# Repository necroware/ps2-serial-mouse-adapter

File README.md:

# PS/2 to Serial Mouse Adapter

Many retro PCs were used with serial port mouse and don't have any PS/2 ports.
Unfortunately most of the serial mice are broken or expensive today. Furthermore
they were mechanical devices with a heavy steel ball to track the movement. This
mechanics got dirty quite fast and was not the best user experience anyway. A
better solution are optical PS/2 mice, most of which unfortunately would not 
work on a serial port. This adapter can be used to connect such a PS/2 mouse to
a serial port of a retro PC.The Adapter is made from through-hole parts only, so
it is very easy to solder and due to Arduino based solution, it is also a very
nice device for tinkering, experimenting and learning about mouse protocols.

## How does it work?

The serial port on the computer communicates with the mouse using basically two
pins - RTS and RX. RTS is used for notification and RX for the actual data
transfer, which contains mouse position, buttons state etcetera. A standard PS/2
mouse on the other hand uses completely incompatible protocol and transfers the
data between the mouse and the computer using the Data and Clock pins. If we
want to connect a PS/2 mouse, to a serial port, we need some instance in
between, to translate between the two different protocols. In this adapter the
translation is done using an Arduino Mini. However, there is another problem.
PS/2 mouse  protocol uses so called TTL logic, which simply means, that the
voltage of 0V means a logical zero and 5V means a logical one. TTL logic is what
Arduino uses as well, but a serial port, or also called RS232, uses another
voltage levels. Any voltage below -3V is a logical one and a voltage above +3V
is a logical zero. So, it is not possible to connect Arduino output directly to
the serial port. It simply will not work and needs another translator, which
converts TTL voltage level to RS232 levels. In this adapter such conversion is
made by a well known MAX232 IC. The software is written in C/C++, it is a simple
Arduino project, which can be used in Arduino Studio as usual.

## How to use?

This project contains everything you need to build your own adapter. You can
use the gerber files to order a PCB. The list of materials is below. After
soldering the adapter, connect the Arduino Mini using an USB to TTL adapter to
your PC and flash the firmware using the Arduino IDE. If you don't know how to
do that, please refer to the documentation of Arduino. 

**ATTENTION!** *The USB port (PWR1) on the adapter is only for powering the
circuits, it is not a data port!*

Connecting the adapter to the PC is very simple. Plug your PS/2 Mouse into the
adapter, connect a mini USB cable to power the adapter. Plug the adapter into a
serial port of your PC. Turn on the PC and use a serial mouse driver of your
choice. The adapter was tested with Microsoft, Logitech and Cute mouse drivers.
Cute Mouse Driver is part of FreeDos project and is free and open source.

## Jumper Settings

There are two jumpers, which can be used to set different modes. Currently you
can choose between 2- and 3-button mouse modes and select so called remote and
streaming mode. Remote mode sends mouse data all the time and has a better
response times in current implementation. Streaming mode sends only data, when
mouse position or button state changes. Unfortunately, this mode is currently
not in a good shape. It has a higher delay and can result in some timing
issues. However, it is interesting to have it for experimental purpose. Default
values are when the jumpers are unset.

JP1 | Setting |Description
----|---------|------------------------------
1-2 | unset   | 3-button Logitech mouse
1-2 | set     | 2-button Microsoft mouse
3-4 | unset   | remote mode
3-4 | set     | streaming mode (experimental)

## Bill of materials

Reference  |#  |LCSC   |Description
-----------|---|-------|------------------------------------------
U1         |1  |       | Arduino Pro Mini 5V (ATMega168 or better)
U2         |1  |C911187| MAX232 or compatible DIP16 package
RS232      |1  |C141882| DB9 female RS232 port
MOUSE1     |1  |C77848 | PS/2 female port
PWR1       |1  |C46398 | Mini-USB port for power supply
C1-5       |5  |C106448| 1µF electrolytic capacitor
R1         |1  |C57436 | 10kOhm resistor (pull-up)
JP1        |1  |       | 2x2 jumper header (optional)

## Known issues

The code is still in development. It works, but it still has some flaws. Timing
is really important in this project and sometimes mouse drivers seem not to get
a response in time from the adapter. Usually just executing the driver once
again will initialize the mouse.

## Tested Mice

If you test the adapter with a mouse, which is not in this list please consider
to submit a report to improve the compatibility of the adapter.

* Logitech Optical Mouse M-BT58 (USB, PS/2, Optical)
* NagerIT Fair Mouse (USB, PS/2, Optical)
* Typthoon Optical Mouse (USB, PS/2, Optical)
* Microsoft IntelliMouse Optical (USB, PS/2, Optical)
* Microsoft IntelliMouse "Classic" (PS/2, Balled)
* Microsoft Basic Optical Mouse (USB, PS/2, Optical, produced 2021)
* Microsoft Comfort Optical Mouse 300 (USB, PS/2, Optical)
* IBM 33G5430 (PS/2, Mechanical)

## Links

* [PS/2 Mouse Protocol description](https://isdaman.com/alsos/hardware/mouse/ps2interface.htm)
* [More PS/2 Mouse Protocol description](http://www-ug.eecg.utoronto.ca/desl/nios_devices_SoC/datasheets/PS2%20Protocol.htm)
* [Serial Mouse Protocol description](https://linux.die.net/man/4/mouse)
* [Cute Mouse Driver](http://cutemouse.sourceforge.net)

## Special Thanks
* creopard from dosreloaded.de for testing with MS IntelliMouse Optical
* moravec from dosreloaded.de for donating the original IBM 33G5430 mechanical mouse

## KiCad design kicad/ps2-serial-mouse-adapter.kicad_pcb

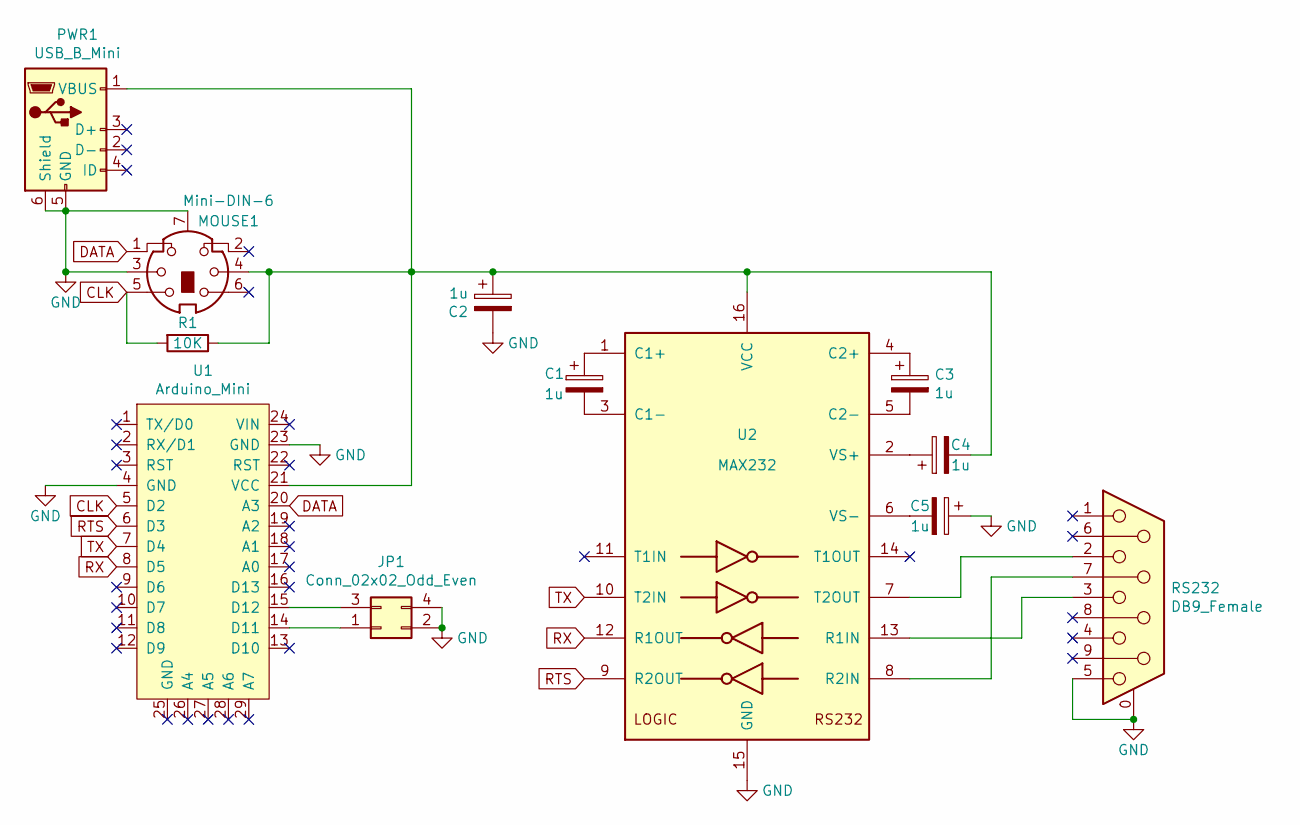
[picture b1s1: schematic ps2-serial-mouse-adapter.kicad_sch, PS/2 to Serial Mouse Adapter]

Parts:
C1, C2, C3, C4, C5: 1u; CP_Radial_D4.0mm_P1.50mm
JP1: Conn_02x02_Odd_Even; PinSocket_2x02_P2.54mm_Vertical
MOUSE1: Mini-DIN-6; Mini_DIN_6_LCSC_C77848; LCSC Part C77848
PWR1: USB_B_Mini; USB_Mini-B-Jing_Extension_LSCS_C46398
R1: 10K; R_Axial_DIN0207_L6.3mm_D2.5mm_P7.62mm_Horizontal; LCSC C57436
RS232: DB9_Female; DSUB-9_Female_Horizontal_P2.77x2.84mm_EdgePinOffset7.70mm_H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
U1: Arduino_Mini; DIP-24_W15.24mm_Socket
U2: MAX232; DIP-16_W7.62mm_Socket; LCSC Part C911187

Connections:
CLK: MOUSE1.5, R1.2, U1.5 (D2)
DATA: MOUSE1.1, U1.20 (A3)
GND: C2.2, C5.1, JP1.2, JP1.4, MOUSE1.3, MOUSE1.7, PWR1.5 (GND), PWR1.6 (Shield), RS232.0 (PAD), RS232.5, U1.4 (GND), U1.23 (GND), U2.15 (GND)
unnamed: C1.1, U2.1 (C1+)
unnamed: C1.2, U2.3 (C1-)
unnamed: C2.1, C4.2, MOUSE1.4, PWR1.1 (VBUS), R1.1, U1.21 (VCC), U2.16 (VCC)
unnamed: C3.1, U2.4 (C2+)
unnamed: C3.2, U2.5 (C2-)
unnamed: C4.1, U2.2 (VS+)
unnamed: C5.2, U2.6 (VS-)
unnamed: JP1.1, U1.14 (D11)
unnamed: JP1.3, U1.15 (D12)
unnamed: RS232.2, U2.7 (T2OUT)
unnamed: RS232.3, U2.13 (R1IN)
unnamed: RS232.7, U2.8 (R2IN)
RTS: U1.6 (D3), U2.9 (R2OUT)
RX: U1.8 (D5), U2.12 (R1OUT)
TX: U1.7 (D4), U2.10 (T2IN)

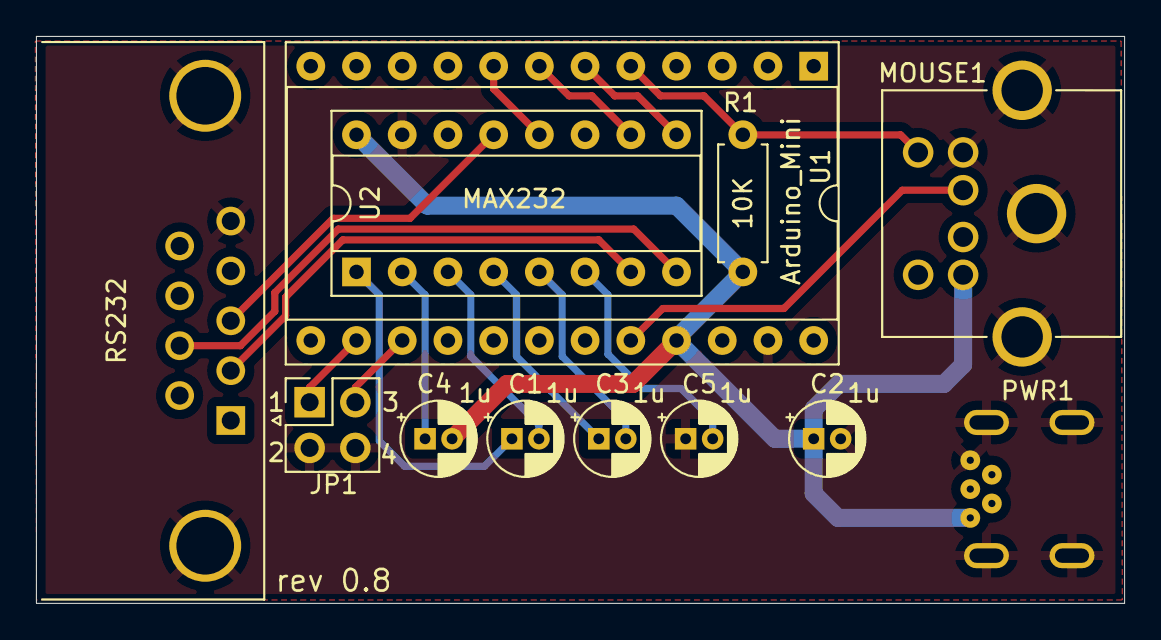
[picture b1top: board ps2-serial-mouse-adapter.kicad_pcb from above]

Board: 2 copper layers, 60.5 x 31.5 mm, 12 parts (0 on the bottom side), 18 nets.

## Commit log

2020-11-21 Shrink PCB
2020-11-21 Move MAX232 under the Arduino to save space
2020-11-22 Add jumpers, fix pwr1
2020-11-22 Update PWR1
2020-11-23 Add gerber files
2020-11-23 Move Kicad files into subfolder
2020-11-23 Move gerber files into subfolder
2020-11-23 Add shim images
2020-11-23 Traces cleanup
2020-11-23 Update gerber files, minor cleanups
2020-11-23 Add necroware kicad library
2020-11-23 Regenrated gerber files
2020-11-23 Update LSCS part number
2020-11-27 Set new submodule path to necroware
2020-12-08 Replace DB9 by DB9_mounting_holes
2020-12-08 Update library
2020-12-08 Fix wrong VCC network
2020-12-08 Add code.
    Just moved from the old local repository
2020-12-08 Removed debug messages and some delays
2020-12-13 Move code into subfolder.
    Else arduino studio complains about the project name
2020-12-13 Rename firmware folder
2020-12-14 Rename shim folder into images
2020-12-14 Add documentation and images
2020-12-14 Documentation formatting
2020-12-14 Fix docu typo
2020-12-14 Add links
2020-12-14 Readme format
2020-12-19 Update links
2020-12-22 Reset on interrupt
2020-12-22 Code cleanup, added sendData/recvData functions
2020-12-22 Use arduino pod types
2020-12-22 Code cleanup
2020-12-22 Move ps2 code into private implementation
2020-12-22 Update list of tested mice
2020-12-23 Move init code into setup function.
    Also improved compatibility with Logitech driver
2020-12-23 Playing with timing for better compatibility
2020-12-27 PS2 mouse interface cleanup
2020-12-29 Add getSettings() function
2020-12-29 Simplified streaming mode switching
2020-12-29 Implement 2-/3-button mode switch
2020-12-29 Add streaming mode switch
2020-12-29 Add jumper documentation
2021-01-10 Add MS mouse to the list of tested devices
2021-01-13 Replace serial DTR through TX.
    DTR was not used anyway and TX can be used in the future for
    communication with the adapter through serial port
2021-01-13 Removed gerber files from the project
2021-01-18 Add IBM Mouse to the list of tested devices
2021-09-02 Fix typos in the readme
2021-10-21 Enable DataReporting in remote mode
2021-10-22 Add a pull-up resistor to the ps/2 clock
2021-11-02 Code clean up, fixed warnings
2021-12-26 Update README.md with tested Microsoft mice
    Added additionaly supported Microsoft mice
2022-01-12 Added LCSC part number for R1
2023-08-22 Updated project to KiCad 6.0.x
2023-08-22 Warnings fixed
2023-08-22 Switched charge pump from GND to VCC
2023-08-22 Update gitignore
